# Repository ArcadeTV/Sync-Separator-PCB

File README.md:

# Sync-Separator-PCB
Eagle printed circuit board for VGA or NTSC/PAL CSYNC to H/V

This is a work-in-progress repo. As of today, 2022/10/22 this is a prototype pcb which has been ordered for further testing.

The circuit is based on a EL1883 which splits the input of a composite sync signal into horizontal and vertical sync to the output-vga-port. This is useful if you have any hardware that outputs CSYNC only and your display device is not happy with that. For example I designed this for using my Atomiswave arcade mainboard on a VGA CRT monitor which expects both H- and V-Sync to be present to work.

As pointed out by by [maki9000](https://circuit-board.de/forum/index.php/User/20222-maki9000/), the EL1883 performs better when it's powered by 3.3V which is why there is an AMS1117 regulator in the BOM. This is likely to be replaced by either a TPS78233DDCR or TLV70033DDCR in future versions.

### Enclosure
[KEMO G026](https://www.kemo-electronic.de/de/Bauelemente/Geh%C3%A4use/Geschlossen/G026N-Gehaeuse-schwarz-ca-72-x-50-x-28-mm.php)

Both sides need a rectangular cut for the vga connectors. 4 PT-screws 3x5mm needed for pcb mounting inside the case.

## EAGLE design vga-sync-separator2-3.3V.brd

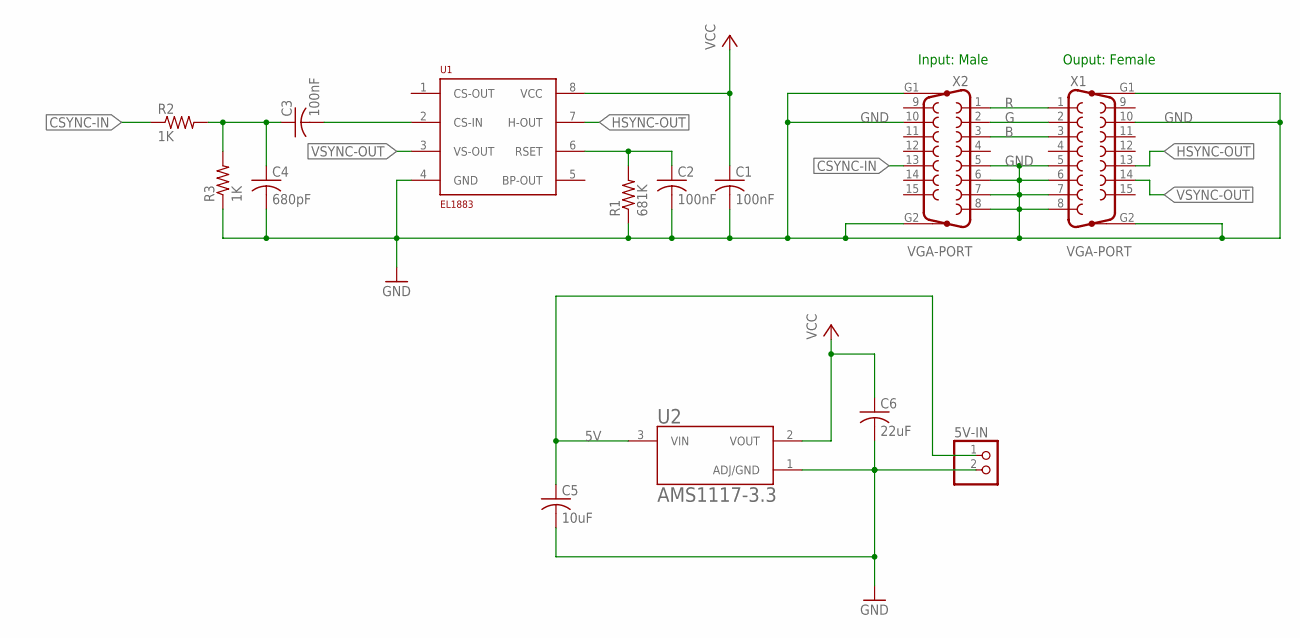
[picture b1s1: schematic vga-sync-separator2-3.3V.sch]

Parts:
5V-IN: PINHD-1X2; 1X02
C1, C2, C3: 100nF; C0805
C4: 680pF; C0805
C5: 10uF; C0805
C6: 22uF; C0805
R1: 681K; R0805
R2, R3: 1K; R0805
U1: EL1883; SO-8
U2: AMS1117-3.3; SOT229P700X180-4N
X1, X2: VGA-PORT; HD15H

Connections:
5V: 5V-IN.1, C5.1, U2.3 (VIN)
B: X1.3, X2.3
CSYNC-IN: R2.1, X2.13
G: X1.2, X2.2
GND: 5V-IN.2, C1.2, C2.2, C4.2, C5.2, C6.2, R1.1, R3.1, U1.4 (GND), U2.1 (ADJ/GND), X1.5, X1.6, X1.7, X1.8, X1.10, X1.G1, X1.G2, X2.5, X2.6, X2.7, X2.8, X2.10, X2.G1, X2.G2
HSYNC-OUT: U1.7 (H-OUT), X1.13
unnamed: C3.2, U1.2 (CS-IN)
unnamed: C3.1, C4.1, R2.2, R3.2
unnamed: C2.1, R1.2, U1.6 (RSET)
R: X1.1, X2.1
VCC: C1.1, C6.1, U1.8 (VCC), U2.2 (VOUT)
VSYNC-OUT: U1.3 (VS-OUT), X1.14

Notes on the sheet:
Input: Male
Ouput: Female

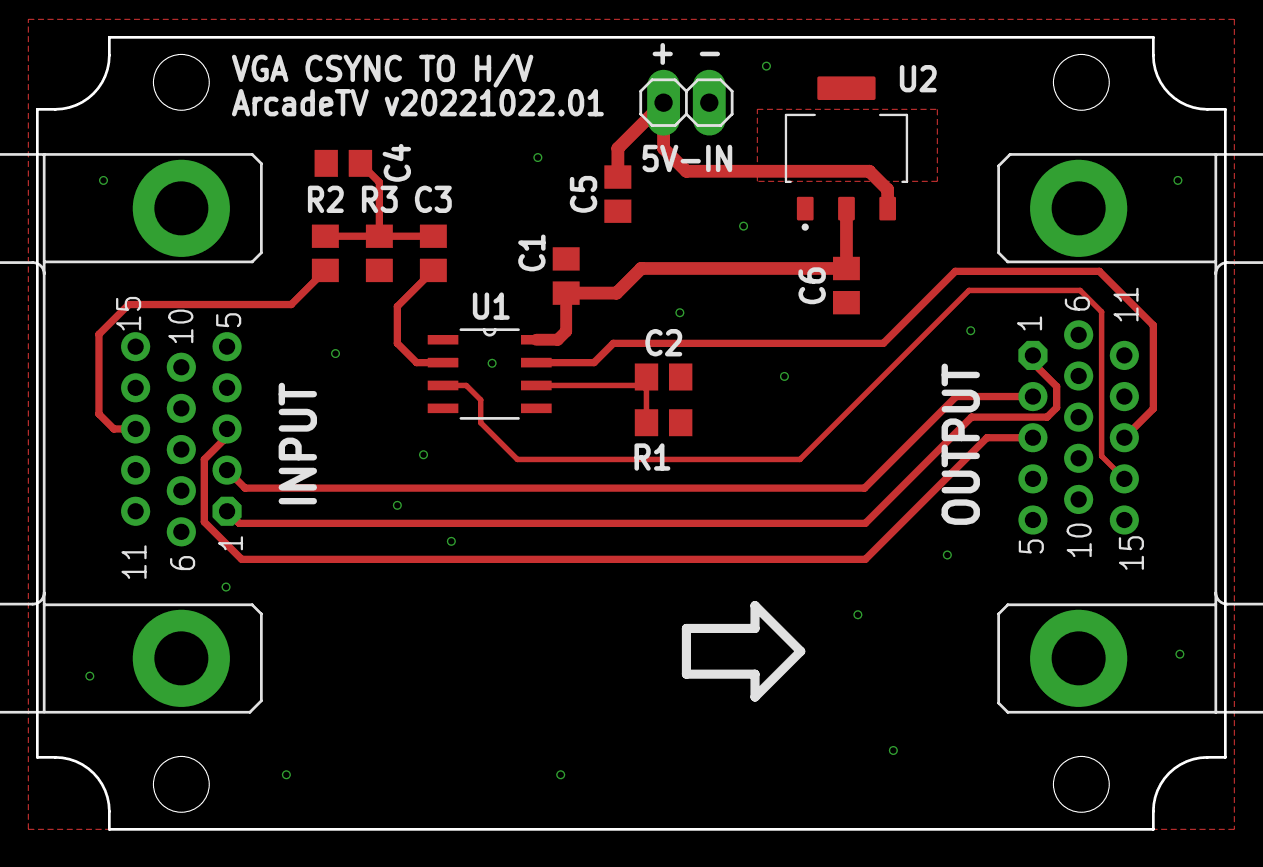
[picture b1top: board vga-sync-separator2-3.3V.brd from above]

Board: 2 copper layers, 66.0 x 44.0 mm, 14 parts (0 on the bottom side), 12 nets.
